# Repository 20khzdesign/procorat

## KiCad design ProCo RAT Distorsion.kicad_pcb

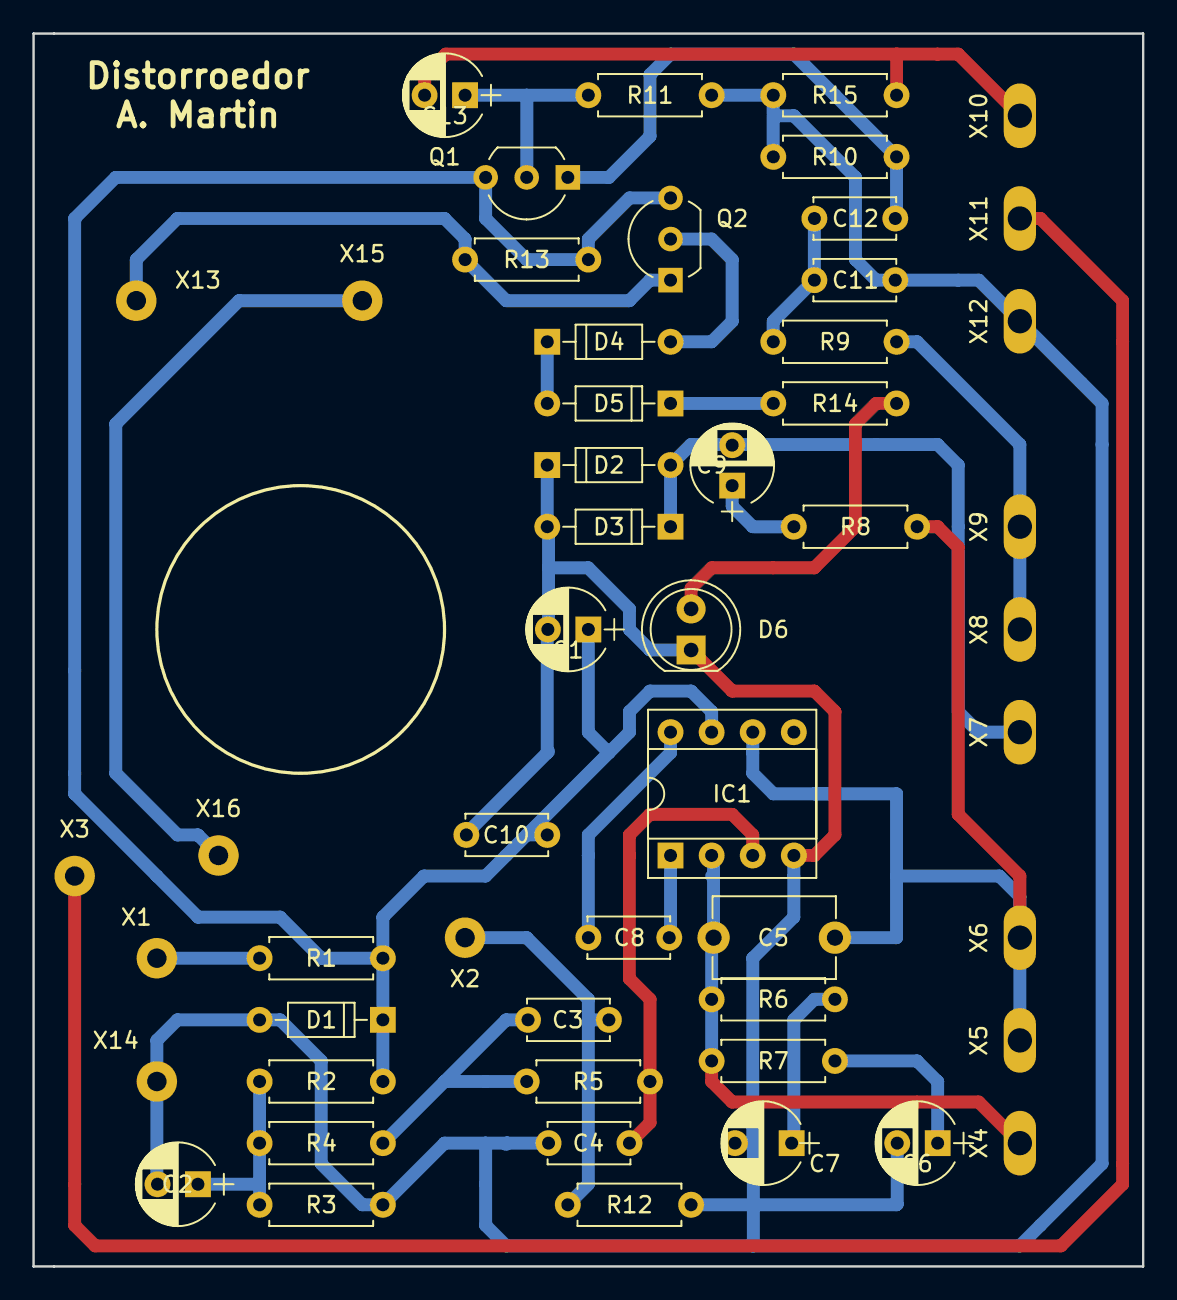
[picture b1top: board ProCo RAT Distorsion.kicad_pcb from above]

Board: 2 copper layers, 68.6 x 76.2 mm, 53 parts (0 on the bottom side), 27 nets.

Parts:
C1: 100u; CP1
C2: 1u; CP1
C3, C12: 22n; C1
C4: 1n; C1
C5: 100p; C_Disc_D7.5mm_W5.0mm_P7.50mm
C6, C9: 4u7; CP1
C7: 2u2; CP2
C8: 30p; C1
C10: 10n; C1
C11: 3n3; C1
C13: 10u; CP1
D1: 1N4004; D_DO-35_SOD27_P7.62mm_Horizontal
D2, D3: D; D_DO-35_SOD27_P7.62mm_Horizontal
D4, D5: 1N4148; D_DO-35_SOD27_P7.62mm_Horizontal
D6: LED; LED_D5.0mm_FlatTop
IC1: LM308; DIP_8
Q1, Q2: BF245; TO-92_Inline_Wide
R1, R6: 47; R
R2, R3: 100K; R
R4: 2,2M; R
R5, R8: 1K; R
R7: 560; R
R9: 1K5; R
R10: 1M; R
R11, R15: 10K; R
R12: 2M2; R
R13: 10M; R
R14: 2K2; R
X1, X2, X3, X13, X14, X15, X16: JD_CONN_01X01; Pad_2,5
X4, X5, X6, X7, X8, X9, X10, X11, X12: JD_CONN_01X01; PAD_OVAL

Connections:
Earth: C1.2, C2.2, C4.2, C6.2, C7.2, C10.2, C11.2, D1.2, D2.1, D3.2, D6.1, IC1.4, R3.1, R10.2, R11.2, R12.2, R15.2, X12.1, X14.1
unnamed: C1.1, C10.1, D1.1, IC1.7, Q1.3, Q2.3, R1.1, R2.2, R13.1
unnamed: C2.1, R2.1, R3.2, R4.1
unnamed: C3.1, R12.1, X2.1
unnamed: C3.2, R4.2, R5.2
unnamed: C4.1, IC1.3, R5.1
unnamed: C5.1, IC1.6, R8.2, X5.1, X6.1
unnamed: C5.2, IC1.2, R6.1, R7.1, X4.1
unnamed: C6.1, R7.2
unnamed: C7.1, R6.2
unnamed: C8.1, IC1.8
unnamed: C8.2, IC1.1
unnamed: C9.1, R8.1
unnamed: C9.2, D2.2, D3.1, X7.1
unnamed: C11.1, C12.1, R9.1
unnamed: C12.2, Q1.1, R10.1
unnamed: C13.1, Q1.2, R11.1
unnamed: C13.2, R15.1, X10.1
unnamed: D4.1, D5.2
unnamed: D4.2, Q2.2
unnamed: D5.1, R14.2
unnamed: D6.2, R14.1
unnamed: R1.2, X1.1
unnamed: R9.2, X8.1, X9.1
unnamed: X3.1, X11.1
unnamed: Q2.1, R13.2, X13.1
unnamed: X15.1, X16.1

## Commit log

2017-09-08 commit inicial
2017-09-26 correcciones y documentacion
